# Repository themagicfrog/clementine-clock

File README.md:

# clementine clock

this is an orange/mandarin-themed clock to set timers & alarms for my room. I decided to make a clock because I usually don't have access
to my phone when I go to sleep at school, and I needed an easy way to know the time and to wake up at the right time. I chose a clementine
theme because I like oranges.

on the main PCB board, there is a 4-digit 7-segment LCD display (showing the time), a small button, and a speaker. there is also wires on the
main PCB board connecting a rotary encoder (adjusting the time) on the top of the orange, a 3 AA battery case, and a big button (snooze & stop) at the
"stem" of the clementine. the case is a 3D-printed cylindrical clementine case.

## bill of materials
| Reference    | Item               | Description                                    | Qty | Unit Price (USD) | Total (USD) | URL |
|--------------|--------------------|------------------------------------------------|-----|-------------------|-------------|-----|
| U1           | Microcontroller    | Seeed XIAO RP2040                              | 1   | 4.68              | 4.68        | https://www.digikey.com/en/products/detail/seeed-technology-co-ltd/102010428/14672129 |
| J1_DISPLAY   | LCD Display        | Grove LCD Screen (104030003)                   | 1   | 6.50              | 6.50        | https://www.digikey.com/en/products/detail/seeed-technology-co-ltd/104030003/5488009 |
| U2           | Voltage Regulator  | MIC5219-3.3YM5 3.3V LDO                        | 1   | 1.19              | 1.19        | https://www.digikey.com/en/products/detail/microchip-technology/MIC5219-3-3YM5-TR/771750 |
| U3           | Audio Amplifier    | PAM8302AAD                                     | 1   | 0.48              | 0.48        | https://www.digikey.com/en/products/detail/diodes-incorporated/pam8302aadcr/4033280 |
| LS1          | Speaker            | SC250708-1 8Ω Speaker                          | 1   | 2.96              | 2.96        | https://www.digikey.com/en/products/detail/db-unlimited/SC250708-1/9990569 |
| SW1          | Rotary Encoder     | ACZ11BR4E-15FD1-20C                             | 1   | 3.22              | 3.22        | https://www.digikey.com/en/products/detail/same-sky-formerly-cui-devices/acz11br4e-15fd1-20c/1923364 |
| SW2          | Pushbutton (Big)   | RP3502ARED                                     | 1   | 2.29              | 2.29        | https://www.digikey.com/en/products/detail/e-switch/RP3502ARED/280448 |
| SW3          | Pushbutton (Small) | Y97HT21A2FAFP                                  | 1   | 0.24              | 0.24        | https://www.digikey.com/en/products/detail/c-k/Y97HT21A2FAFP/3861375 |
| SW4          | Power Switch       | PCM12SMTR slide SPST                           | 1   | 1.14              | 1.14        | https://www.digikey.com/en/products/detail/c-k/PCM12SMTR/1640112 |
| BT1_HOLDER   | Battery Holder     | Kitronik 2273 3×AAA w/ JST                     | 1   | 1.87              | 1.87        | https://www.digikey.com/en/products/detail/kitronik-ltd/2273/8635437 |
| BT1          | Battery Connector  | B2B-PH-K-S JST-PH 2-pin header                 | 1   | 0.10              | 0.10        | https://www.digikey.com/en/products/detail/jst-sales-america-inc/B2B-PH-K-S/926611 |
| J1           | LCD Header         | PRPC004SAAN-RC 1×4 2.54mm                      | 1   | 0.34              | 0.34        | https://www.digikey.com/en/products/detail/adam-tech/RS1-04-G/9829303 |
| C1           | Capacitor          | 10µF 10V X7R 0805                               | 1   | 1.02              | 1.02        | https://www.digikey.com/en/products/detail/kemet/c0805x106j8rac7210/7423434 |
| C2           | Capacitor          | 22µF 10V X5R 0805                               | 1   | 0.15              | 0.15        | https://www.digikey.com/en/products/detail/yageo/CC0805MKX5R7BB226/5195308 |
| C3           | Capacitor          | 0.22µF 50V X7R 0805                             | 1   | 0.15              | 0.15        | https://www.digikey.com/en/products/detail/kemet/c0805c224k5ractu/754753 |
| C4           | Capacitor          | 1µF 50V X7R 0805                                | 1   | 0.81              | 0.81        | https://www.digikey.com/en/products/detail/kemet/C0805C105K5RACTU/3317615 |
| C5           | Capacitor          | 10nF 250V 0805                                  | 1   | 0.08              | 0.08        | https://www.digikey.com/en/products/detail/kemet/C0805C103F5GECAUTO/8647276 |
| C6           | Capacitor          | 4.7µF 50V X5R 0805                              | 1   | 0.19              | 0.19        | https://www.digikey.com/en/products/detail/murata-electronics/grm21br61h475ke51l/4905540 |
| R1           | Resistor           | 100kΩ 1% 0805                                   | 1   | 0.10              | 0.10        | https://www.digikey.com/en/products/detail/stackpole-electronics-inc/rmcf0805ft100k/1760712 |
| R2           | Resistor           | 1kΩ 1% 0805                                     | 1   | 0.10              | 0.10        | https://www.digikey.com/en/products/detail/stackpole-electronics-inc/rmcf0805ft1k00/1760090 |
| D1           | LED                | Red 0805 LED                                    | 1   | 0.19              | 0.19        | https://www.digikey.com/en/products/detail/würth-elektronik/150080RS75000/4489918 |
| **TOTAL**    | —                  | —                                              | —   | **Tax + Shipping = 3.12** | **44.26** | |

## made for [Blueprint](https://blueprint.hackclub.com/)
## find the Journal (devlogs) and project on Blueprint [here](https://blueprint.hackclub.com/projects/2563)

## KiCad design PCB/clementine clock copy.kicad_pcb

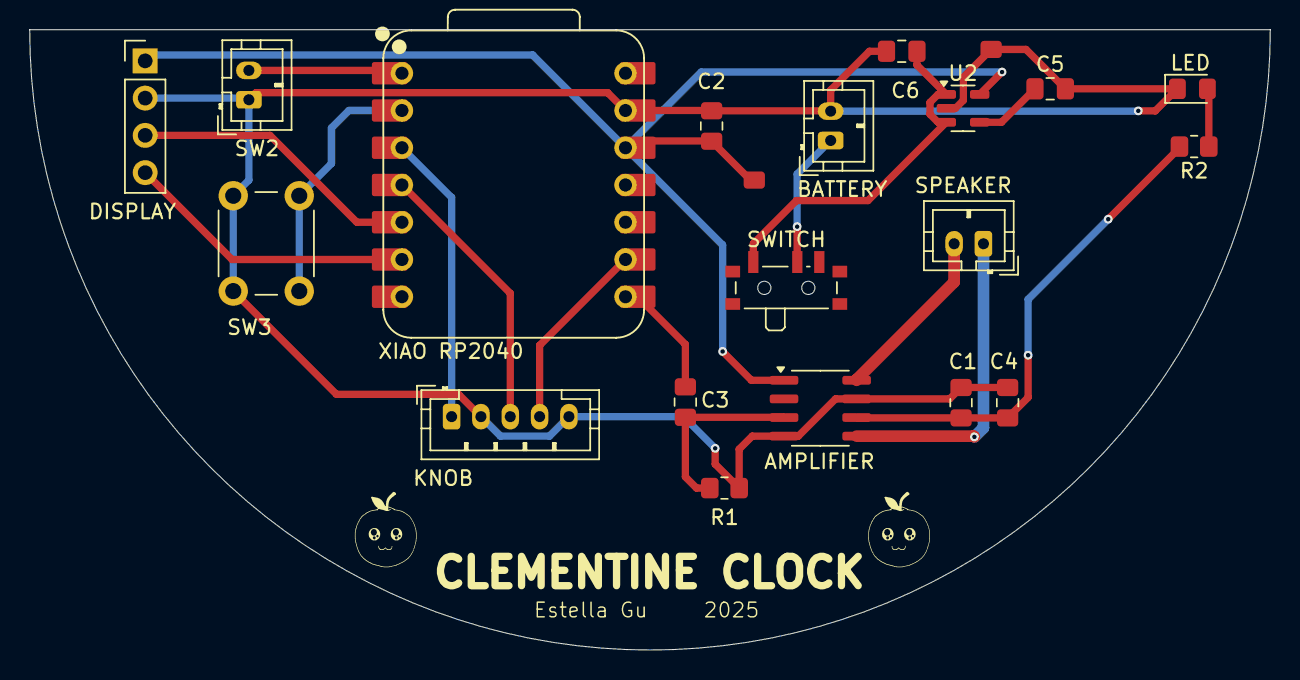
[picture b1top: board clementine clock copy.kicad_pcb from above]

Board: 2 copper layers, 84.6 x 42.3 mm, 19 parts (0 on the bottom side), 17 nets.

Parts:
AMPLIFIER: PAM8302AAD; SOIC-8_3.9x4.9mm_P1.27mm
BATTERY: 4.5V (3xAA); JST_PH_B2B-PH-K_1x02_P2.00mm_Vertical
C1: 10 µF; C_0805_2012Metric_Pad1.18x1.45mm_HandSolder
C2: 22µF; C_0805_2012Metric_Pad1.18x1.45mm_HandSolder
C3: 0.22uF; C_0805_2012Metric_Pad1.18x1.45mm_HandSolder
C4: 1uF; C_0805_2012Metric_Pad1.18x1.45mm_HandSolder
C5: 10nF; C_0805_2012Metric_Pad1.18x1.45mm_HandSolder
C6: 4.7uF; C_0805_2012Metric_Pad1.18x1.45mm_HandSolder
DISPLAY: LCD _Screen; PinHeader_1x04_P2.54mm_Vertical
KNOB: RotaryEncoder_Switch; JST_PH_B5B-PH-K_1x05_P2.00mm_Vertical
LED: LED; LED_0805_2012Metric_Pad1.15x1.40mm_HandSolder
R1: 100k; R_0805_2012Metric_Pad1.20x1.40mm_HandSolder
R2: 1k; R_0805_2012Metric_Pad1.20x1.40mm_HandSolder
SPEAKER: Speaker; JST_PH_B2B-PH-K_1x02_P2.00mm_Vertical
SW2: SW_Push; JST_PH_B2B-PH-K_1x02_P2.00mm_Vertical
SW3: SW_Push; SW_PUSH_6mm
SW4: SW_SPST; SW_SPDT_PCM12
U2: MIC5219-3.3YM5; SOT-23-5
XIAO RP2040: XIAO-RP2040-DIP

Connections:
/3V3: AMPLIFIER.1 (~SD), AMPLIFIER.6 (VDD), C1.1, C2.1, C4.1, DISPLAY.1, R2.2, U2.5 (OUT), XIAO RP2040.12 (3V3)
/ENC_BTN: KNOB.4 (S1), XIAO RP2040.9 (GPIO2/SCK)
/GND: AMPLIFIER.4 (IN-), AMPLIFIER.7 (GND), BATTERY.2 (-), C1.2, C2.2, C4.2, C5.2, C6.1, DISPLAY.2, KNOB.2 (C), KNOB.5 (S2), LED.1 (K), R1.1, SW2.1, SW3.1, U2.2 (GND), XIAO RP2040.13 (GND)
/GPIO28: KNOB.1 (A), XIAO RP2040.3 (GPIO28/ADC2/A2)
/GPIO29: KNOB.3 (B), XIAO RP2040.4 (GPIO29/ADC3/A3)
/SCL: DISPLAY.4, XIAO RP2040.6 (GPIO7/SCL)
/SDA: DISPLAY.3, XIAO RP2040.5 (GPIO6/SDA)
unnamed: BATTERY.1 (+), SW4.2 (B)
unnamed: LED.2 (A), R2.1
unnamed: C6.2, SW4.1 (A), U2.1 (IN), U2.3 (EN)
unnamed: C3.1, XIAO RP2040.8 (GPIO1/RX)
unnamed: SW2.2, XIAO RP2040.1 (GPIO26/ADC0/A0)
unnamed: SW3.2, XIAO RP2040.2 (GPIO27/ADC1/A1)
unnamed: C5.1, U2.4 (BP)
unnamed: AMPLIFIER.3 (IN+), C3.2, R1.2
unnamed: AMPLIFIER.5 (OUT+), SPEAKER.1
unnamed: AMPLIFIER.8 (OUT-), SPEAKER.2

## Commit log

2025-12-01 init
2025-12-01 add bom
2025-12-02 add gerbers
